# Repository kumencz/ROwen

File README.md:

# Reflow Owen
Reflow soldering heater project for FEKT VUT Brno

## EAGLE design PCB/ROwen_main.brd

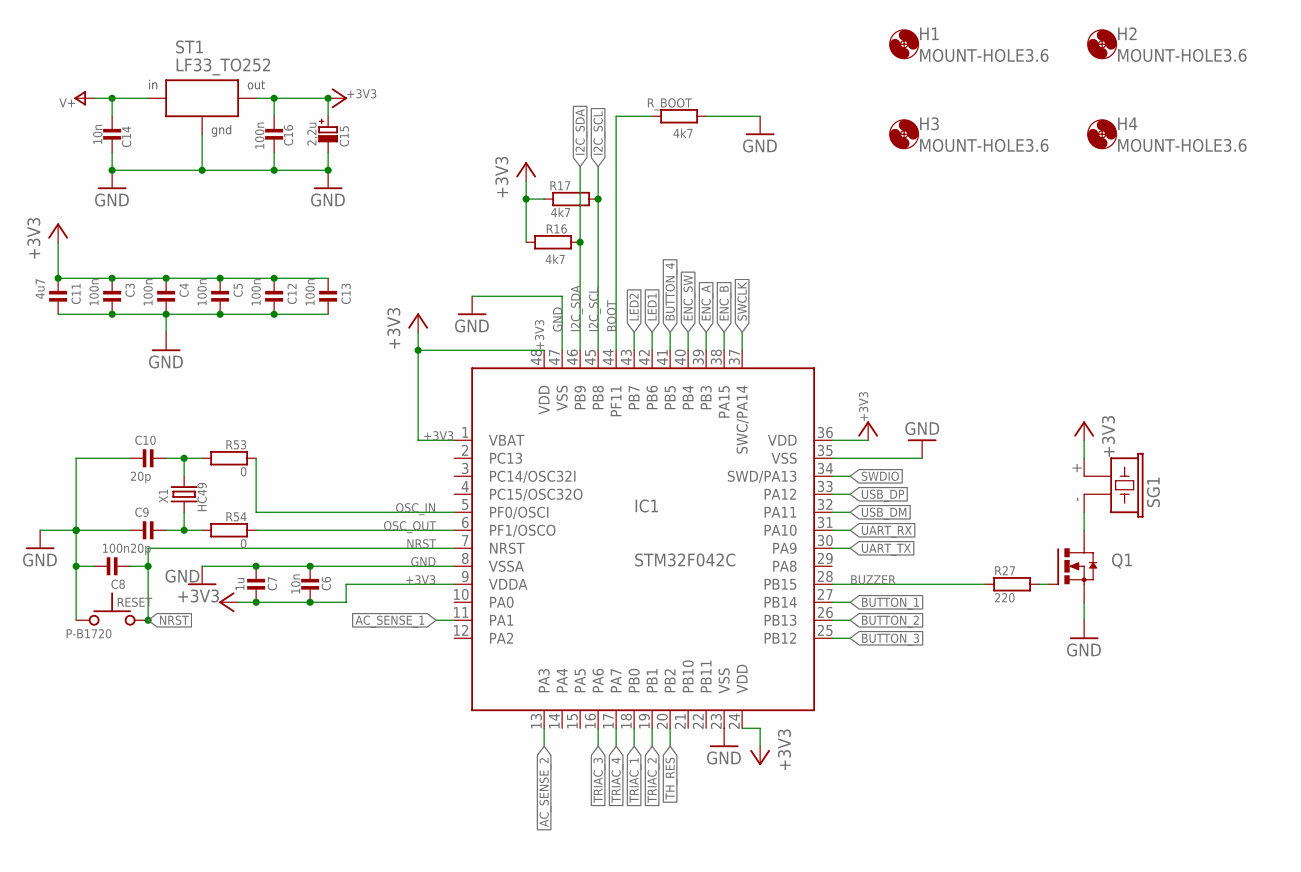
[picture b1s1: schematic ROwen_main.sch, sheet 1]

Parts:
C3, C4, C5, C8, C12, C13, C16: 100n; 0603
C6, C14: 10n; 0603
C7: 1u; 0603
C9, C10: 20p; 0603
C11: 4u7; 0603
C15: 2,2u; ER_08,5_05
H1, H2, H3, H4: MOUNT-HOLE3.6; 3,6
IC1: STM32F042C; LQFP48
Q1: N-HEXFET-2D_SOT232-IRLL014N; SOT223
R16, R17: 4k7; 0603
R27: 220; 0603
R53, R54: 0; 0603
RESET: P-B1720
R_BOOT: 4k7; 0603
SG1: F/CM12P
ST1: LF33_TO252; DPACK
X1: HC49; X_HC49/S

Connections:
+3V3: C3.2, C4.2, C5.2, C6.1, C7.1, C11.2, C12.2, C13.2, C15.+, C16.2, IC1.1 (VBAT), IC1.9 (VDDA), IC1.24 (VDD), IC1.36 (VDD), IC1.48 (VDD), R16.2, R17.2, SG1.+ (1), ST1.3 (OUT); also elsewhere on the board
AC_SENSE_1: IC1.11 (PA1); also elsewhere on the board
AC_SENSE_2: IC1.13 (PA3); also elsewhere on the board
BOOT: IC1.44 (PF11), R_BOOT.2
BUTTON_1: IC1.27 (PB14); also elsewhere on the board
BUTTON_2: IC1.26 (PB13); also elsewhere on the board
BUTTON_3: IC1.25 (PB12); also elsewhere on the board
BUTTON_4: IC1.41 (PB5); also elsewhere on the board
BUZZER: IC1.28 (PB15), R27.1
ENC_A: IC1.39 (PB3); also elsewhere on the board
ENC_B: IC1.38 (PA15); also elsewhere on the board
ENC_SW: IC1.40 (PB4); also elsewhere on the board
GND: C3.1, C4.1, C5.1, C6.2, C7.2, C8.1, C9.2, C10.2, C11.1, C12.1, C13.1, C14.2, C15.-, C16.1, IC1.8 (VSSA), IC1.23 (VSS), IC1.35 (VSS), IC1.47 (VSS), Q1.3 (S), RESET.1, R_BOOT.1, ST1.2 (GND); also elsewhere on the board
I2C_SCL: IC1.45 (PB8), R17.1; also elsewhere on the board
I2C_SDA: IC1.46 (PB9), R16.1; also elsewhere on the board
LED1: IC1.42 (PB6); also elsewhere on the board
LED2: IC1.43 (PB7); also elsewhere on the board
unnamed: Q1.2 (D), Q1.4 (D), SG1.- (2)
unnamed: Q1.1 (G), R27.2
unnamed: C9.1, R54.2, X1.1
unnamed: C10.1, R53.2, X1.2
NRST: C8.2, IC1.7 (NRST), RESET.2; also elsewhere on the board
OSC_IN: IC1.5 (PF0/OSCI), R53.1
OSC_OUT: IC1.6 (PF1/OSCO), R54.1
SWCLK: IC1.37 (SWC/PA14); also elsewhere on the board
SWDIO: IC1.34 (SWD/PA13); also elsewhere on the board
TH_RES: IC1.20 (PB2); also elsewhere on the board
TRIAC_1: IC1.18 (PB0); also elsewhere on the board
TRIAC_2: IC1.19 (PB1); also elsewhere on the board
TRIAC_3: IC1.16 (PA6); also elsewhere on the board
TRIAC_4: IC1.17 (PA7); also elsewhere on the board
UART_RX: IC1.31 (PA10); also elsewhere on the board
UART_TX: IC1.30 (PA9); also elsewhere on the board
USB_DM: IC1.32 (PA11); also elsewhere on the board
USB_DP: IC1.33 (PA12); also elsewhere on the board
V+: C14.1, ST1.1 (IN); also elsewhere on the board

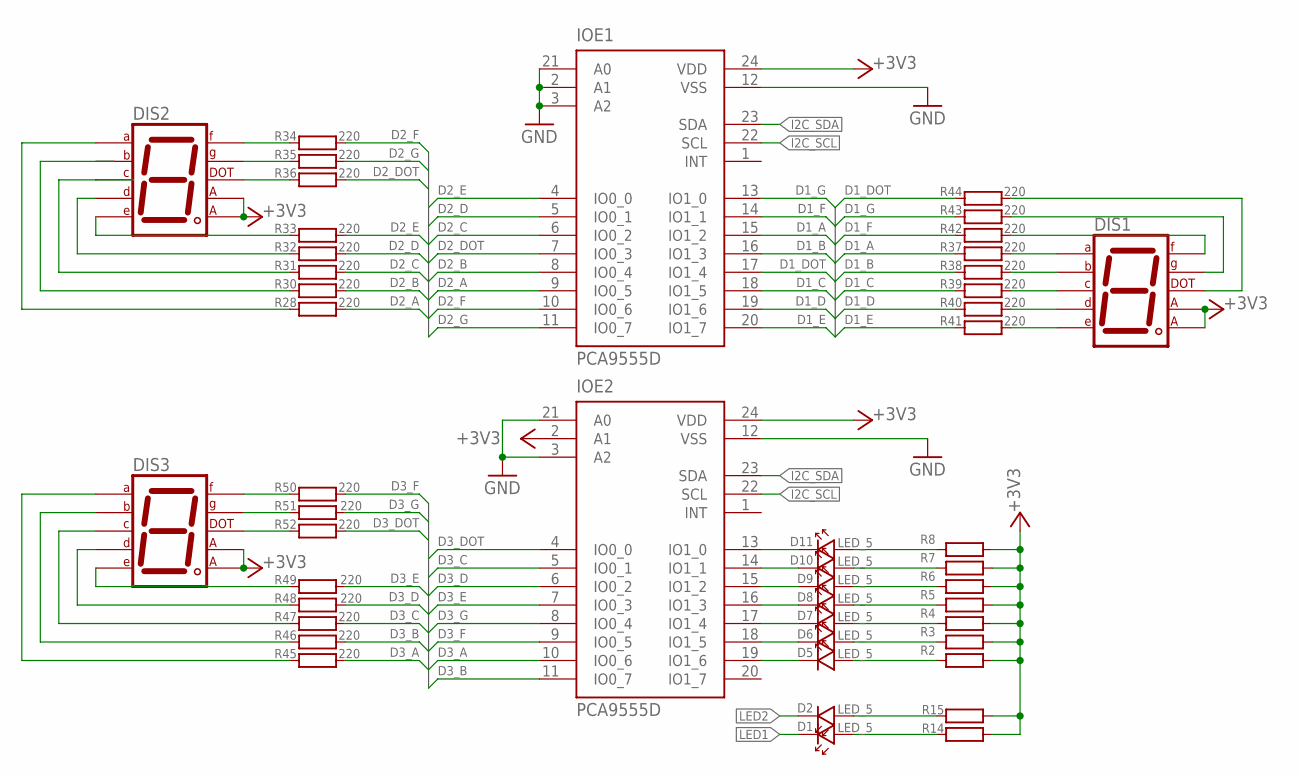
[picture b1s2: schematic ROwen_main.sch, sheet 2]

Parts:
D1, D2, D5, D6, D7, D8, D9, D10, D11: LED_5
DIS1, DIS2, DIS3: 7-SEGMENT-CA-0.56"; 7_SEGMENT_0.56"
IOE1, IOE2: PCA9555D; SO24
R2, R3, R4, R5, R6, R7, R8, R14, R15: R_R0603; 0603
R28, R30, R31, R32, R33, R34, R35, R36, R37, R38, R39, R40, R41, R42, R43, R44, R45, R46, R47, R48, R49, R50, R51, R52: 220; 0603

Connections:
+3V3: DIS1.3 (CA2), DIS1.8 (CA1), DIS2.3 (CA2), DIS2.8 (CA1), DIS3.3 (CA2), DIS3.8 (CA1), IOE1.24 (VDD), IOE2.2 (A1), IOE2.24 (VDD), R2.2, R3.2, R4.2, R5.2, R6.2, R7.2, R8.2, R14.2, R15.2; also elsewhere on the board
D1_A: IOE1.15 (IO1_2), R37.2
D1_B: IOE1.16 (IO1_3), R38.2
D1_C: IOE1.18 (IO1_5), R39.2
D1_D: IOE1.19 (IO1_6), R40.2
D1_DOT: IOE1.17 (IO1_4), R44.2
D1_E: IOE1.20 (IO1_7), R41.2
D1_F: IOE1.14 (IO1_1), R42.2
D1_G: IOE1.13 (IO1_0), R43.2
D2_A: IOE1.9 (IO0_5), R28.2
D2_B: IOE1.8 (IO0_4), R30.2
D2_C: IOE1.6 (IO0_2), R31.2
D2_D: IOE1.5 (IO0_1), R32.2
D2_DOT: IOE1.7 (IO0_3), R36.2
D2_E: IOE1.4 (IO0_0), R33.2
D2_F: IOE1.10 (IO0_6), R34.2
D2_G: IOE1.11 (IO0_7), R35.2
D3_A: IOE2.10 (IO0_6), R45.2
D3_B: IOE2.11 (IO0_7), R46.2
D3_C: IOE2.5 (IO0_1), R47.2
D3_D: IOE2.6 (IO0_2), R48.2
D3_DOT: IOE2.4 (IO0_0), R52.2
D3_E: IOE2.7 (IO0_3), R49.2
D3_F: IOE2.9 (IO0_5), R50.2
D3_G: IOE2.8 (IO0_4), R51.2
GND: IOE1.2 (A1), IOE1.3 (A2), IOE1.12 (VSS), IOE1.21 (A0), IOE2.3 (A2), IOE2.12 (VSS), IOE2.21 (A0); also elsewhere on the board
I2C_SCL: IOE1.22 (SCL), IOE2.22 (SCL); also elsewhere on the board
I2C_SDA: IOE1.23 (SDA), IOE2.23 (SDA); also elsewhere on the board
LED1: D1.K; also elsewhere on the board
LED2: D2.K; also elsewhere on the board
unnamed: DIS1.7 (A), R37.1
unnamed: DIS1.6 (B), R38.1
unnamed: DIS1.4 (C), R39.1
unnamed: DIS1.2 (D), R40.1
unnamed: DIS1.1 (E), R41.1
unnamed: DIS1.9 (F), R42.1
unnamed: DIS2.7 (A), R28.1
unnamed: DIS2.6 (B), R30.1
unnamed: DIS2.4 (C), R31.1
unnamed: DIS2.2 (D), R32.1
unnamed: DIS2.1 (E), R33.1
unnamed: DIS2.9 (F), R34.1
unnamed: DIS2.10 (G), R35.1
unnamed: DIS3.7 (A), R45.1
unnamed: DIS3.6 (B), R46.1
unnamed: DIS3.4 (C), R47.1
unnamed: DIS3.2 (D), R48.1
unnamed: DIS3.1 (E), R49.1
unnamed: DIS3.9 (F), R50.1
unnamed: DIS3.10 (G), R51.1
unnamed: DIS3.5 (DP), R52.1
unnamed: D11.A, R8.1
unnamed: D10.A, R7.1
unnamed: D8.A, R5.1
unnamed: D6.A, R3.1
unnamed: D5.A, R2.1
unnamed: D7.A, R4.1
unnamed: D9.A, R6.1
unnamed: D5.K, IOE2.19 (IO1_6)
unnamed: D6.K, IOE2.18 (IO1_5)
unnamed: D7.K, IOE2.17 (IO1_4)
unnamed: D8.K, IOE2.16 (IO1_3)
unnamed: D9.K, IOE2.15 (IO1_2)
unnamed: D10.K, IOE2.14 (IO1_1)
unnamed: D11.K, IOE2.13 (IO1_0)
unnamed: D2.A, R15.1
unnamed: D1.A, R14.1
unnamed: DIS1.10 (G), R43.1
unnamed: DIS1.5 (DP), R44.1
unnamed: DIS2.5 (DP), R36.1

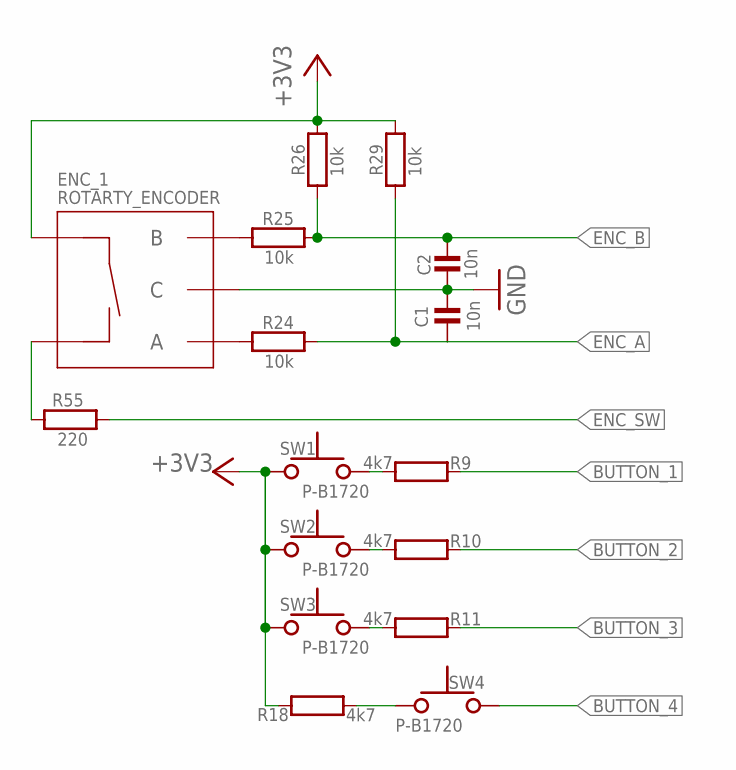
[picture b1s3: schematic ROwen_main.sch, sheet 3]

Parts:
C1, C2: 10n; 0603
ENC_1: ROTARTY_ENCODER; ROTARY_ENC_PLAIN
R9, R10, R11, R18: 4k7; 0603
R24, R25, R26, R29: 10k; 0603
R55: 220; 0603
SW1, SW2, SW3, SW4: P-B1720

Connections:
+3V3: ENC_1.SW+, R18.1, R26.1, R29.1, SW1.1, SW2.1, SW3.1; also elsewhere on the board
BUTTON_1: R9.1; also elsewhere on the board
BUTTON_2: R10.1; also elsewhere on the board
BUTTON_3: R11.1; also elsewhere on the board
BUTTON_4: SW4.1; also elsewhere on the board
ENC_A: C1.2, R24.1, R29.2; also elsewhere on the board
ENC_B: C2.1, R25.1, R26.2; also elsewhere on the board
ENC_SW: R55.2; also elsewhere on the board
GND: C1.1, C2.2, ENC_1.C; also elsewhere on the board
unnamed: R9.2, SW1.2
unnamed: R10.2, SW2.2
unnamed: R11.2, SW3.2
unnamed: R18.2, SW4.2
unnamed: ENC_1.B, R25.2
unnamed: ENC_1.A, R24.2
unnamed: ENC_1.SW-, R55.1

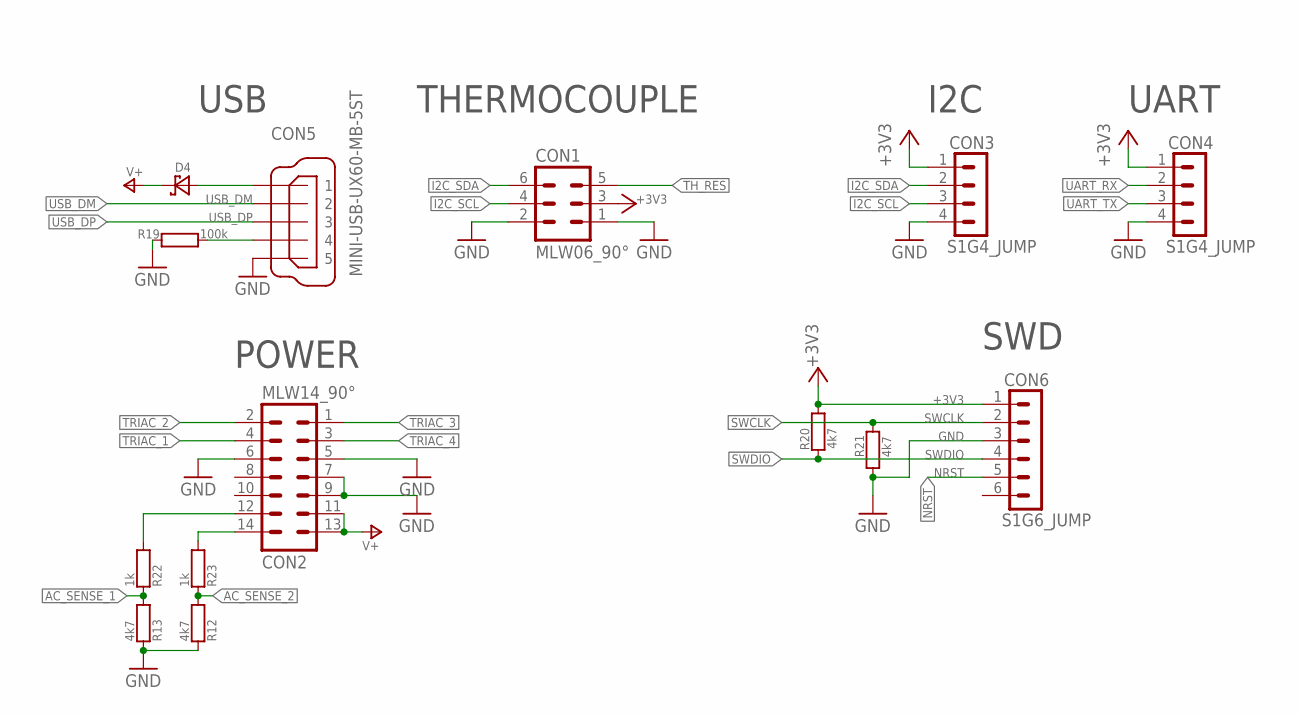
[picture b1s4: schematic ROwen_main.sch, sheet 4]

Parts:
CON1: MLW06_90°; MLW06A
CON2: MLW14_90°; MLW14A
CON3, CON4: S1G4_JUMP; S1G4_JUM
CON5: MINI-USB-UX60-MB-5ST; UX60-MB-5ST
CON6: S1G6_JUMP; S1G6_JUM
D4: D_SCHOTKY_SMA; D_SMA
R12, R13, R20, R21: 4k7; 0603
R19: 100k; 0603
R22, R23: 1k; 0603

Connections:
+3V3: CON1.3, CON3.1, CON4.1, CON6.1, R20.2; also elsewhere on the board
AC_SENSE_1: R13.2, R22.1; also elsewhere on the board
AC_SENSE_2: R12.2, R23.1; also elsewhere on the board
GND: CON1.1, CON1.2, CON2.5, CON2.6, CON2.7, CON2.9, CON3.4, CON4.4, CON5.5, CON6.3, R12.1, R13.1, R19.1, R21.1; also elsewhere on the board
I2C_SCL: CON1.4, CON3.3; also elsewhere on the board
I2C_SDA: CON1.6, CON3.2; also elsewhere on the board
unnamed: CON5.1, D4.A
unnamed: CON5.4, R19.2
NRST: CON6.5; also elsewhere on the board
SINUS_A: CON2.12, R22.2
SINUS_B: CON2.14, R23.2
SWCLK: CON6.2, R21.2; also elsewhere on the board
SWDIO: CON6.4, R20.1; also elsewhere on the board
TH_RES: CON1.5; also elsewhere on the board
TRIAC_1: CON2.4; also elsewhere on the board
TRIAC_2: CON2.2; also elsewhere on the board
TRIAC_3: CON2.1; also elsewhere on the board
TRIAC_4: CON2.3; also elsewhere on the board
UART_RX: CON4.2; also elsewhere on the board
UART_TX: CON4.3; also elsewhere on the board
USB_DM: CON5.2; also elsewhere on the board
USB_DP: CON5.3; also elsewhere on the board
V+: CON2.11, CON2.13, D4.K; also elsewhere on the board

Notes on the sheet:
I2C
UART
SWD
THERMOCOUPLE
POWER
USB

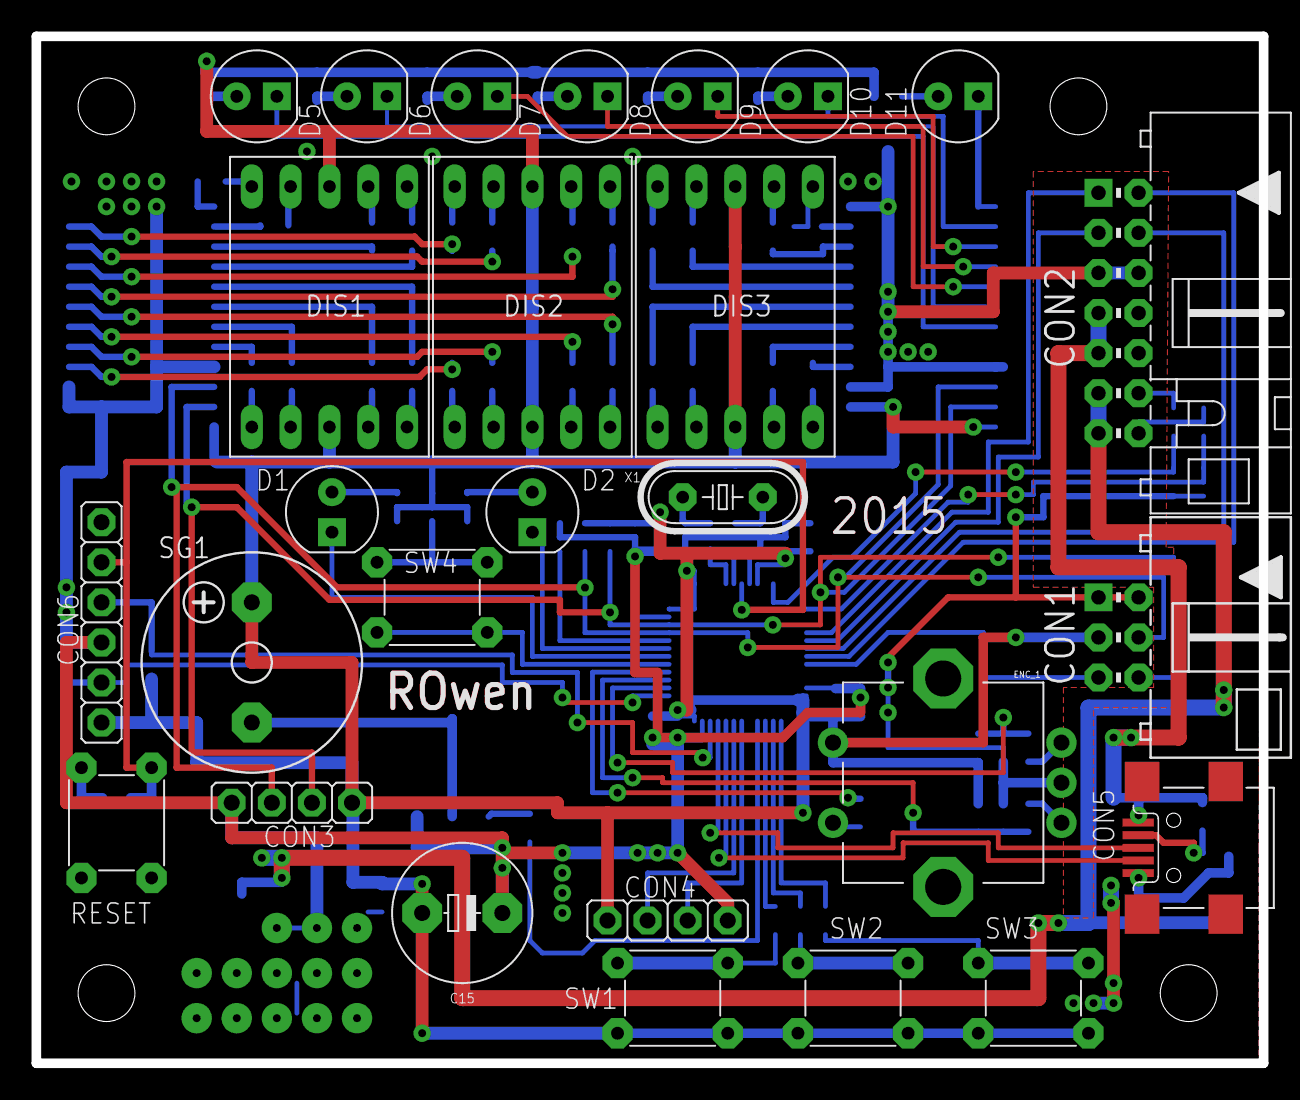
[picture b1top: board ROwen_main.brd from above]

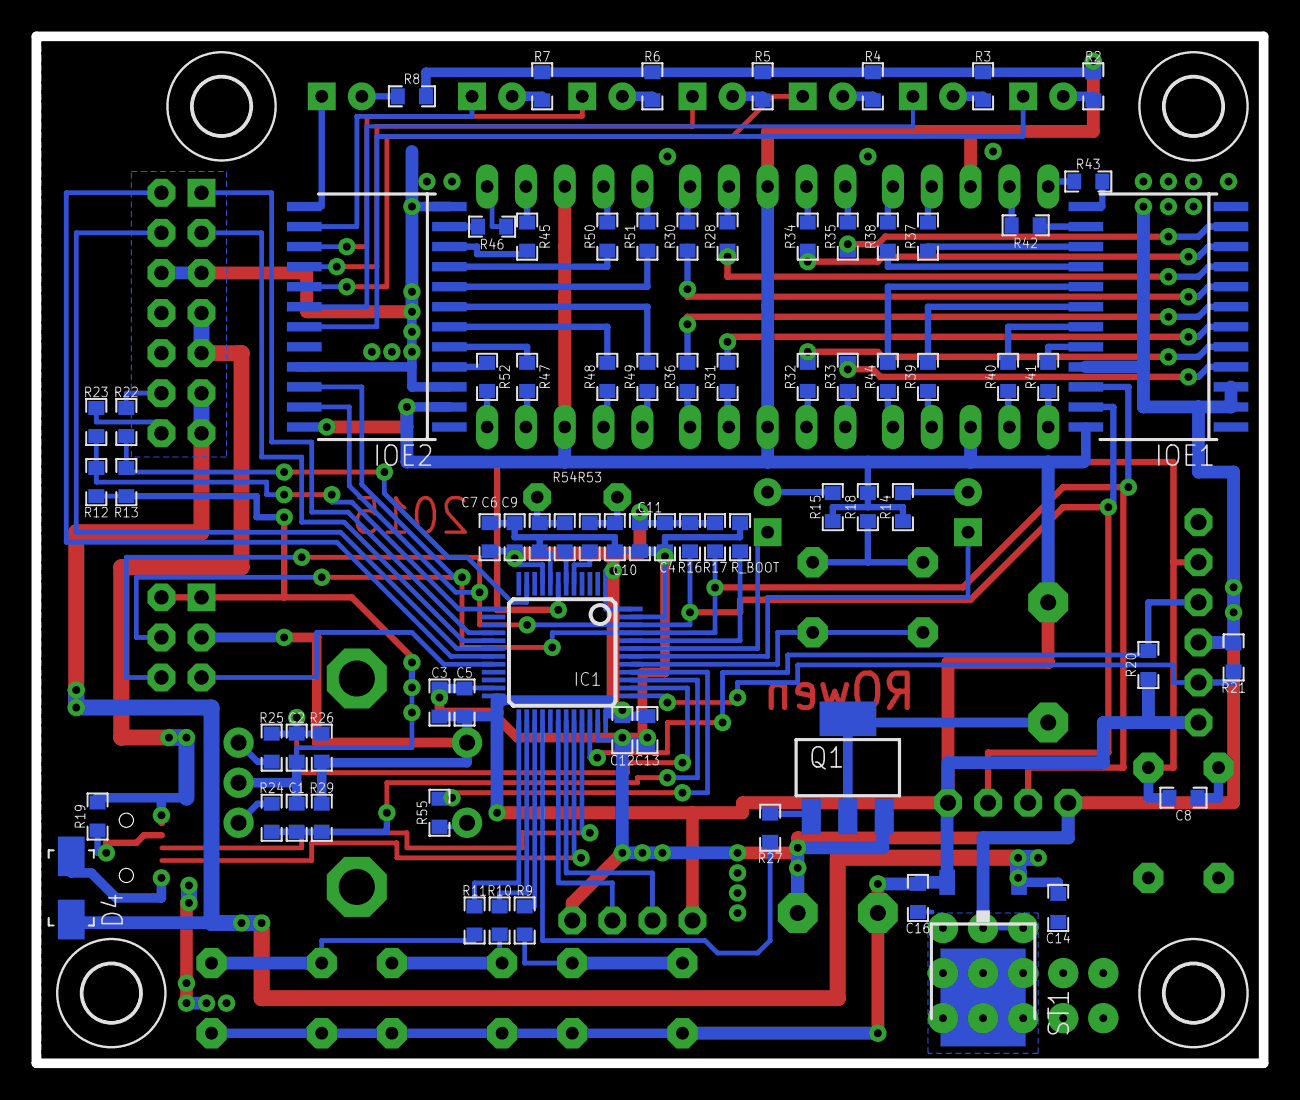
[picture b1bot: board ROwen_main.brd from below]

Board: 2 copper layers, 77.8 x 65.1 mm, 107 parts (80 on the bottom side), 111 nets.

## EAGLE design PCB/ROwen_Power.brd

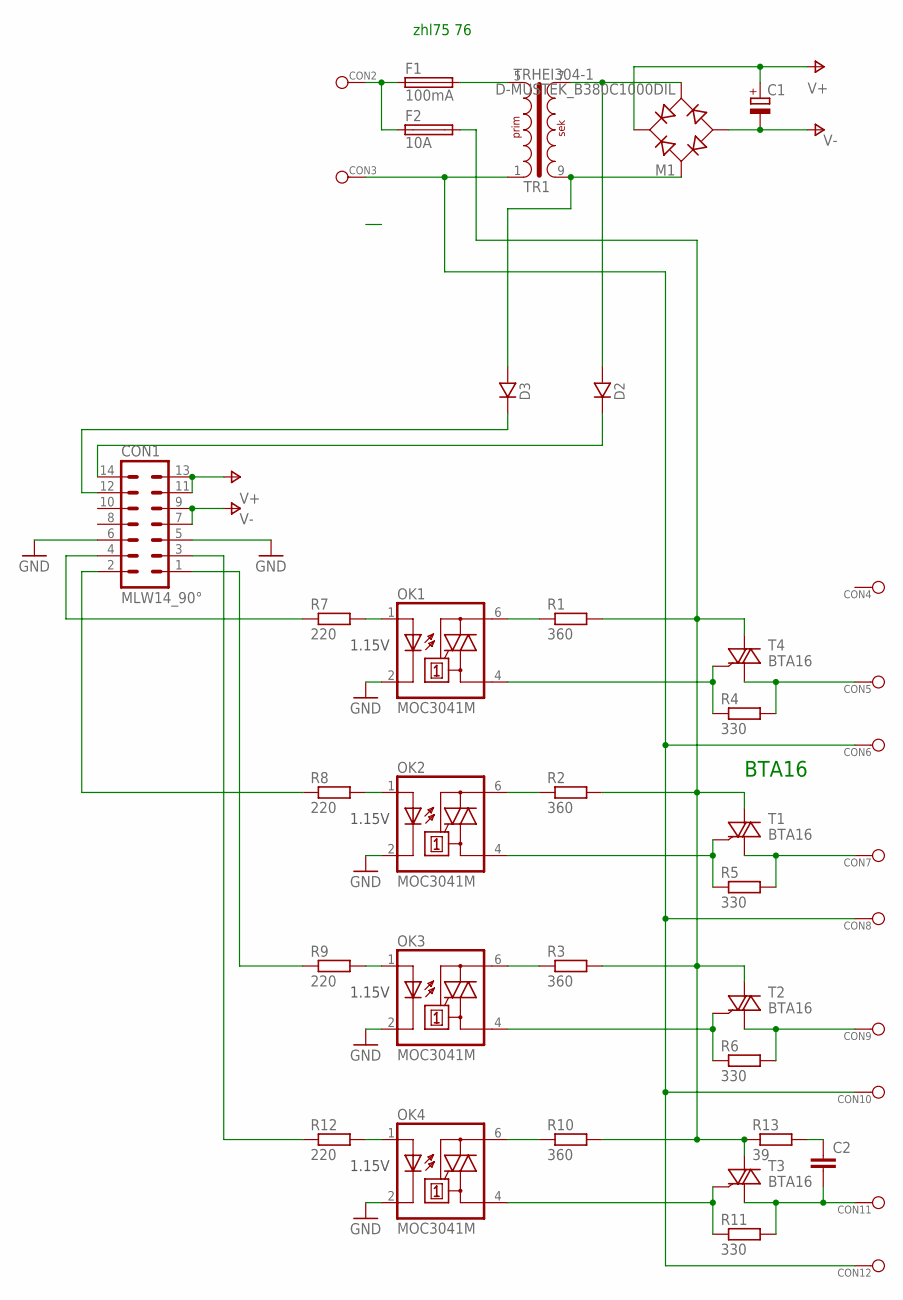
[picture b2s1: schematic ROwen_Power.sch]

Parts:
C1: CPOL-EUE3.5-10; E3,5-10
C2: C-EU050-055X075; C050-055X075
CON1: MLW14_90°; MLW14A
CON2, CON3, CON4, CON5, CON6, CON7, CON8, CON9, CON10, CON11, CON12: WAGO256
D2, D3: D_10; DO41
F1: 100mA; SH22,5A
F2: 10A; SH22,5A
M1: D-MUSTEK_B380C1000DIL; DM_DB1
OK1, OK2, OK3, OK4: MOC3041M; DIL06
R1, R2, R3, R10: 360; 0207/10
R4, R5, R6, R11: 330; 0207/10
R7, R8, R9, R12: 220; 0207/10
R13: 39; 0309/12
T1, T2, T3, T4: BTA16; TO220
TR1: TRHEI304-1; TRHEI304

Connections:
GND: CON1.5, CON1.6, OK1.2 (C), OK2.2 (C), OK3.2 (C), OK4.2 (C)
unnamed: CON1.1, R9.1
unnamed: OK1.6 (A2), R1.1
unnamed: CON5.1, R4.2, T4.T1 (A1)
unnamed: OK3.4 (A1), R6.1, T2.G
unnamed: OK2.4 (A1), R5.1, T1.G
unnamed: OK3.1 (A), R9.2
unnamed: OK3.6 (A2), R3.1
unnamed: CON7.1, R5.2, T1.T1 (A1)
unnamed: OK1.4 (A1), R4.1, T4.G
unnamed: CON1.4, R7.1
unnamed: OK2.6 (A2), R2.1
unnamed: CON9.1, R6.2, T2.T1 (A1)
unnamed: F1.2, TR1.5 (P2)
unnamed: OK2.1 (A), R8.2
unnamed: OK1.1 (A), R7.2
unnamed: CON2.1, F1.1, F2.1
unnamed: F2.2, R1.2, R2.2, R3.2, R10.2, R13.1, T1.T2 (A2), T2.T2 (A2), T3.T2 (A2), T4.T2 (A2)
unnamed: D3.A, M1.AC1, TR1.9 (S2)
unnamed: CON3.1, CON6.1, CON8.1, CON10.1, CON12.1, TR1.1
unnamed: D2.A, M1.AC2, TR1.7 (S1)
unnamed: CON1.2, R8.1
unnamed: C2.1, R13.2
unnamed: C2.2, CON11.1, R11.2, T3.T1 (A1)
unnamed: OK4.4 (A1), R11.1, T3.G
unnamed: CON1.14, D2.K
unnamed: CON1.12, D3.K
unnamed: OK4.6 (A2), R10.1
unnamed: OK4.1 (A), R12.2
unnamed: CON1.3, R12.1
V+: C1.+, CON1.11, CON1.13, M1.+
V-: C1.-, CON1.7, CON1.9, M1.-

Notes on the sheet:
BTA16
1.15V
zhl75 76

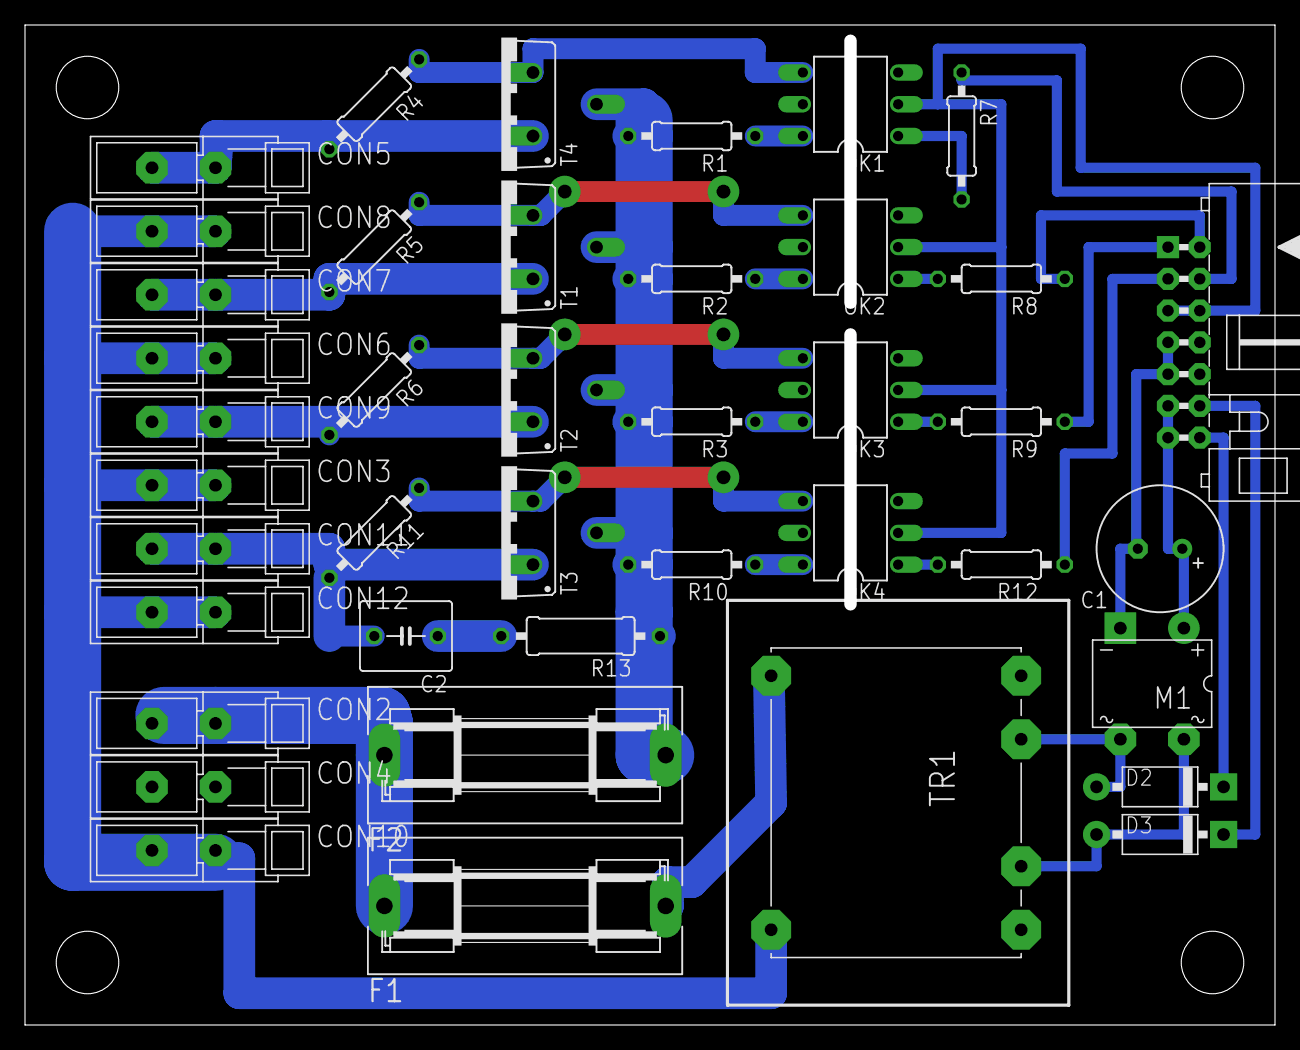
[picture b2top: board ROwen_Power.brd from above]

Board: 2 copper layers, 99.0 x 79.0 mm, 41 parts (0 on the bottom side), 32 nets.

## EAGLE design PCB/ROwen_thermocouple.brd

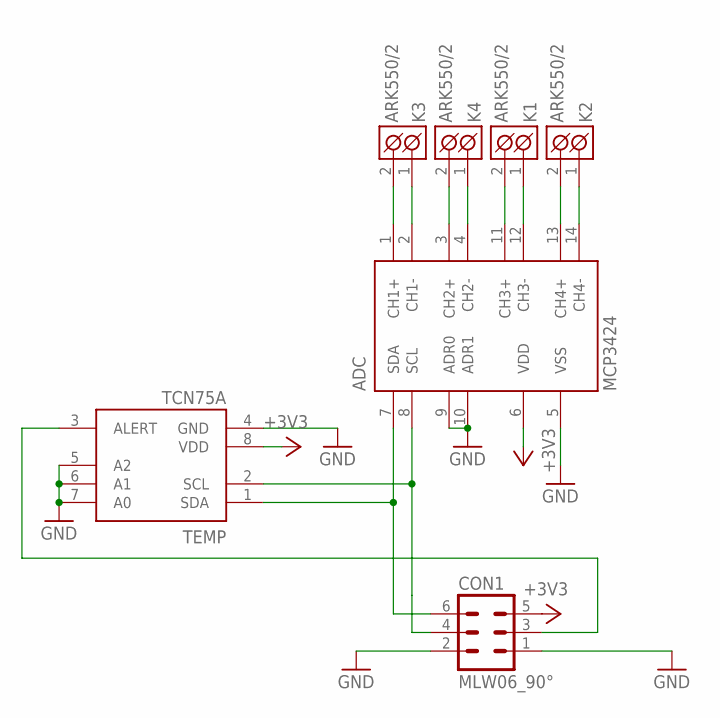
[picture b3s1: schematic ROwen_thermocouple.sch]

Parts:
ADC: MCP3424; TSSOP14
CON1: MLW06_90°; MLW06A
K1, K2, K3, K4: ARK550/2
TEMP: TCN75A; SO8

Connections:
+3V3: ADC.6 (VDD), CON1.5, TEMP.8 (VDD)
GND: ADC.5 (VSS), ADC.9 (ADR0), ADC.10 (ADR1), CON1.1, CON1.2, TEMP.4 (GND), TEMP.5 (A2), TEMP.6 (A1), TEMP.7 (A0)
unnamed: ADC.12 (CH3-), K1.1 (K1)
unnamed: ADC.11 (CH3+), K1.2 (K2)
unnamed: ADC.14 (CH4-), K2.1 (K1)
unnamed: ADC.13 (CH4+), K2.2 (K2)
unnamed: ADC.2 (CH1-), K3.1 (K1)
unnamed: ADC.1 (CH1+), K3.2 (K2)
unnamed: ADC.4 (CH2-), K4.1 (K1)
unnamed: ADC.3 (CH2+), K4.2 (K2)
unnamed: CON1.3, TEMP.3 (ALERT)
unnamed: ADC.8 (SCL), CON1.4, TEMP.2 (SCL)
unnamed: ADC.7 (SDA), CON1.6, TEMP.1 (SDA)

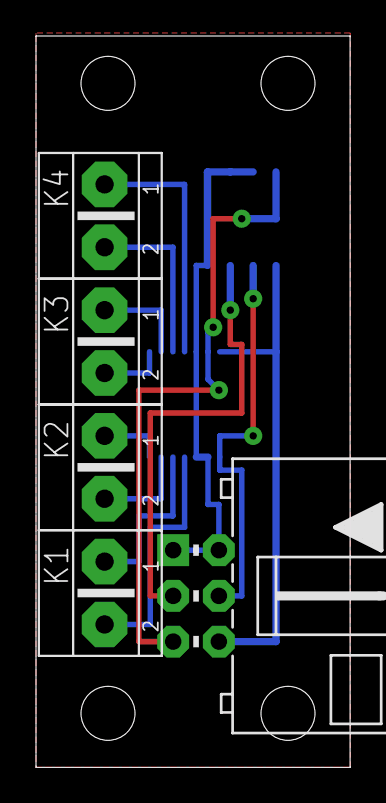
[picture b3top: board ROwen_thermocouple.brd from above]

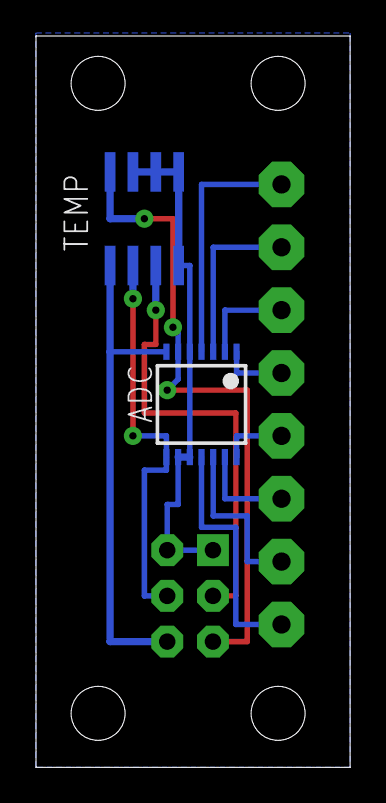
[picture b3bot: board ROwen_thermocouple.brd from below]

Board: 2 copper layers, 17.4 x 40.6 mm, 7 parts (2 on the bottom side), 13 nets.

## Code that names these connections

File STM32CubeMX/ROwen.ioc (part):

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Mcu.Name=STM32F051C8Tx
Mcu.Package=LQFP48
Mcu.UserName=STM32F051C8Tx
PA1.GPIOParameters=GPIO_Label,GPIO_PuPd,GPIO_Mode
PA1.GPIO_Label=AC_SENSE_1
PA1.GPIO_Mode=GPIO_MODE_ANALOG
PA1.GPIO_PuPd=GPIO_NOPULL
PA1.Mode=INP
PA1.Signal=COMP1_INP
PA10.Mode=Asynchronous
PA10.Signal=USART1_RX
PA13.Mode=Serial-WireDebug
PA13.Signal=SYS_SWDIO
PA14.Mode=Serial-WireDebug
PA14.Signal=SYS_SWCLK
PA15.GPIOParameters=GPIO_Label,GPIO_ModeDefaultEXTI,GPIO_PuPd
PA15.GPIO_Label=ENC_A
PA15.GPIO_ModeDefaultEXTI=GPIO_MODE_IT_RISING
PA15.GPIO_PuPd=GPIO_PULLDOWN
PA15.Signal=GPXTI15
PA3.GPIOParameters=GPIO_Label,GPIO_PuPd,GPIO_Mode
PA3.GPIO_Label=AC_SENSE_2
PA3.GPIO_Mode=GPIO_MODE_ANALOG
PA3.GPIO_PuPd=GPIO_NOPULL
PA3.Mode=INP
PA3.Signal=COMP2_INP
PA6.GPIOParameters=GPIO_Label,GPIO_Speed,GPIO_ModeDefaultPP,GPIO_PuPd
PA6.GPIO_Label=TRIAC_3
PA6.GPIO_ModeDefaultPP=GPIO_MODE_AF_PP
PA6.GPIO_PuPd=GPIO_NOPULL
PA6.GPIO_Speed=GPIO_SPEED_HIGH
PA6.Signal=S_TIM3_CH1
PA7.GPIOParameters=GPIO_Label,GPIO_Speed,GPIO_ModeDefaultPP,GPIO_PuPd
PA7.GPIO_Label=TRIAC_4
PA7.GPIO_ModeDefaultPP=GPIO_MODE_AF_PP
PA7.GPIO_PuPd=GPIO_NOPULL
PA7.GPIO_Speed=GPIO_SPEED_HIGH
PA7.Signal=S_TIM3_CH2
PA9.Mode=Asynchronous
PA9.Signal=USART1_TX
PB0.GPIOParameters=GPIO_Label,GPIO_Speed,GPIO_ModeDefaultPP,GPIO_PuPd
PB0.GPIO_Label=TRIAC_1
PB0.GPIO_ModeDefaultPP=GPIO_MODE_AF_PP
PB0.GPIO_PuPd=GPIO_NOPULL
PB0.GPIO_Speed=GPIO_SPEED_HIGH
PB0.Signal=S_TIM3_CH3
PB1.GPIOParameters=GPIO_Label,GPIO_Speed,GPIO_ModeDefaultPP,GPIO_PuPd
PB1.GPIO_Label=TRIAC_2
PB1.GPIO_ModeDefaultPP=GPIO_MODE_AF_PP
PB1.GPIO_PuPd=GPIO_NOPULL
PB1.GPIO_Speed=GPIO_SPEED_HIGH
PB1.Signal=S_TIM3_CH4
PB12.GPIOParameters=GPIO_Label,GPIO_ModeDefaultEXTI,GPIO_PuPd
PB12.GPIO_Label=BUTTON_3
PB12.GPIO_ModeDefaultEXTI=GPIO_MODE_IT_RISING
PB12.GPIO_PuPd=GPIO_PULLDOWN
PB12.Signal=GPXTI12
PB13.GPIOParameters=GPIO_Label,GPIO_ModeDefaultEXTI,GPIO_PuPd
PB13.GPIO_Label=BUTTON_2
PB13.GPIO_ModeDefaultEXTI=GPIO_MODE_IT_RISING
PB13.GPIO_PuPd=GPIO_PULLDOWN
PB13.Signal=GPXTI13
PB14.GPIOParameters=GPIO_Label,GPIO_ModeDefaultEXTI,GPIO_PuPd
PB14.GPIO_Label=BUTTON_1
PB14.GPIO_ModeDefaultEXTI=GPIO_MODE_IT_RISING
PB14.GPIO_PuPd=GPIO_PULLDOWN
PB14.Signal=GPXTI14
PB15.GPIOParameters=GPIO_ModeDefaultOutputPP,GPIO_Label,GPIO_Speed,GPIO_PuPd
PB15.GPIO_Label=BUZZER
PB15.GPIO_ModeDefaultOutputPP=GPIO_MODE_OUTPUT_PP
PB15.GPIO_PuPd=GPIO_PULLUP
PB15.GPIO_Speed=GPIO_SPEED_HIGH
PB15.Signal=GPIO_Output
PB2.GPIOParameters=GPIO_Label,GPIO_PuPd,GPIO_Mode
PB2.GPIO_Label=TH_RES
PB2.GPIO_Mode=GPIO_MODE_INPUT
PB2.GPIO_PuPd=GPIO_PULLDOWN
PB2.Signal=GPIO_Input
PB3.GPIOParameters=GPIO_Label,GPIO_PuPd,GPIO_Mode
PB3.GPIO_Label=ENC_B
PB3.GPIO_Mode=GPIO_MODE_INPUT
PB3.GPIO_PuPd=GPIO_PULLDOWN
PB3.Signal=GPIO_Input
PB4.GPIOParameters=GPIO_Label,GPIO_ModeDefaultEXTI,GPIO_PuPd
PB4.GPIO_Label=ENC_SW
PB4.GPIO_ModeDefaultEXTI=GPIO_MODE_IT_RISING
PB4.GPIO_PuPd=GPIO_PULLDOWN
PB4.Signal=GPXTI4
PB5.GPIOParameters=GPIO_Label,GPIO_ModeDefaultEXTI,GPIO_PuPd
PB5.GPIO_Label=BUTTON_4
PB5.GPIO_ModeDefaultEXTI=GPIO_MODE_IT_RISING
PB5.GPIO_PuPd=GPIO_PULLDOWN
PB5.Signal=GPXTI5
PB6.GPIOParameters=GPIO_Label,GPIO_ModeDefaultOutputPP,GPIO_FM6,GPIO_Speed,GPIO_PuPd
PB6.GPIO_FM6=__NULL
PB6.GPIO_Label=LED_1
PB6.GPIO_ModeDefaultOutputPP=GPIO_MODE_OUTPUT_PP
PB6.GPIO_PuPd=GPIO_PULLUP
PB6.GPIO_Speed=GPIO_SPEED_HIGH
PB6.Signal=GPIO_Output
PB7.GPIOParameters=GPIO_Label,GPIO_ModeDefaultOutputPP,GPIO_Speed,GPIO_PuPd,GPIO_FM7
PB7.GPIO_FM7=__NULL
PB7.GPIO_Label=LED_2
PB7.GPIO_ModeDefaultOutputPP=GPIO_MODE_OUTPUT_PP
PB7.GPIO_PuPd=GPIO_PULLUP
PB7.GPIO_Speed=GPIO_SPEED_HIGH
PB7.Signal=GPIO_Output
PB8.Mode=I2C
PB8.Signal=I2C1_SCL
PB9.Mode=I2C
PB9.Signal=I2C1_SDA
PF0-OSC_IN.Mode=HSE-External-Oscillator
PF0-OSC_IN.Signal=RCC_OSC_IN
PF1-OSC_OUT.Mode=HSE-External-Oscillator
PF1-OSC_OUT.Signal=RCC_OSC_OUT
RCC.SYSCLKFreq_VALUE=8000000

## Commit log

2015-03-30 Initial PCB design
2015-03-31 small PCB updates
2015-03-31 README update
2015-04-10 Polygon improvement
2015-04-10 Polygon improvement 2
2015-04-14 Manufactured version
2015-04-14 GND polygon separated
2015-04-16 Main PCB measerements
2015-04-18 Added STM32CubeMX configuration for STM32F051
2015-04-18 Added .gitignore file
2015-04-18 Corected .gitignore
2015-04-18 Initial code commit
2015-04-23 Prepare for communication
2015-04-29 Prepare for ADC
2015-04-29 Move HAL version code to own folder
2015-04-29 .gitignore update
2015-04-29 Clean working project Keil's 5.14 CMSIS pack and ST's Standard Peripherals Library 1.5.0
2015-05-02 LEDs, buttons, encoder, buzzer initialization and basic function
2015-05-02 Initial i2c support for "i2c expander", tcn75a temp, MCP344 ADC
2015-05-03 Float temp for TCN75a
2015-05-03 Init ADC, MCU voltage, MCU temp
2015-05-03 Main file cleared
2015-05-03 UART sending temps
2015-05-03 i2c sessions enumerated
2015-05-03 UART prepare for TX direction interrupt
2015-05-04 ADC measure, TRIAC TIM Init
2015-05-04 Temp on display
2015-05-05 Display complete, basic triacs control , code cleaning
2015-05-06 Display repair for one digit
2015-05-06 Project files update
2015-05-06 Display fix for zero number
2015-05-06 Human readable UART output
2015-05-09 Underclock to 8MHz, Triac PWM on 1Hz
2015-05-10 Power PCB scheme cleared
2015-05-10 Uart receive prepare, Triacs PWM repair
2016-02-20 Encoder handling rewrited
    Code cleaning
2016-02-20 Project changes
2016-02-29 Display support for decimal numbers. Automatic precision.
2016-02-29 Reading all 4 channels from thermocouple ADC
2016-03-02 Controlling of top LEDs + project file changes
2016-04-24 Triacs power control only in 100 steps.
2016-04-24 HMI power control only in 100 steps + LED bargraph function.
2016-04-24 Removed HAL code
2016-04-24 Text support for display
2016-04-24 Thermocouple read rate at 15 SPS with 0,2C resolution [MCP3424]
2016-05-12 NEW Display menu
2020-12-23 Files reorganized
2020-12-23 Added 3D printable case stl files
2020-12-23 Added BOM and basic documentation
2020-12-23 Added old PCB renders
2020-12-23 Src files relocated
2020-12-23 Added STM32CubeIDE project files and GCC linker file
2020-12-23 Keil project files updated
2020-12-23 PID, Profile ramps, Fan ... forgotten development commit
2020-12-23 Manual temperature set finished and working, other small improvements and fixes
2021-08-02 Manual duty control implemented

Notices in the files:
parts and their libraries:
Copyright (C) PaJa 2001-2011
Copyright (C) PaJa 2011
